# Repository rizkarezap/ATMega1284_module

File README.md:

# ATMega1284 Module
We found that we faced challenges when we got a project that prioritized board size, periperal, and resources. Therefore, we designed a module to facilitate our work. This module uses ATMega1284 as the main control. We also added CP2102 as USB to UART Bridge Virtual COM Port (VCP) drivers. We use a 20MHz oscillator and expand all the ATMega1284 peripherals.

# Board Design
We use KiCAD to design our boards. We include everything for you to be able to develop again.

# Our hope
Actually we really want to print this module. However, we have limited research and resource costs. If you are willing to help us, we will be very grateful. Furthermore, we present everything we have done. Hope you can use it.

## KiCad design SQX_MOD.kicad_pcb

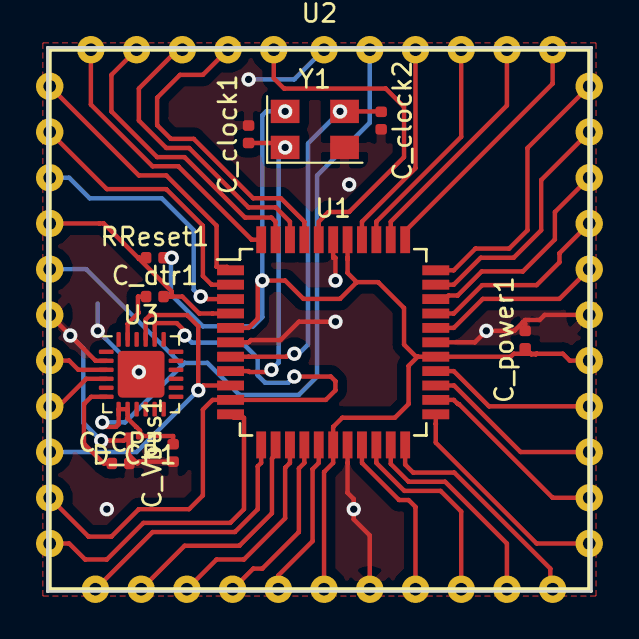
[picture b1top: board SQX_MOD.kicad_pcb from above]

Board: 2 copper layers, 30.2 x 30.2 mm, 12 parts (0 on the bottom side), 42 nets.

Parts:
C_CP1: 100nF; C_0402_1005Metric
C_Vbus1: 4.7pf; C_0402_1005Metric
C_clock1, C_clock2: 22pf; C_0402_1005Metric
C_dtr1: 100Nf; C_0402_1005Metric
C_power1: 100nF; C_0402_1005Metric
D_CP1: D_TVS; D_0201_0603Metric
RReset1: 10K; R_0402_1005Metric
U1: ATmega1284P-AU; TQFP-44_10x10mm_P0.8mm
U2: SQX_MOD; SQX_MOD_SMD
U3: CP2102N-A01-GQFN24; QFN-24-1EP_4x4mm_P0.5mm_EP2.6x2.6mm
Y1: Crystal_GND24; Crystal_SMD_5032-4Pin_5.0x3.2mm

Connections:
AREF: U1.29, U2.AREF
D+: U2.D+, U3.3
D-: U2.D-, U3.4
DTR: C_dtr1.1, U3.23
GND: C_CP1.2, C_Vbus1.1, C_clock1.2, C_clock2.2, C_power1.2, D_CP1.2, U1.6, U1.18, U1.28, U1.39, U2.GND0, U2.GND1, U2.GND2, U2.GND3, U3.2, U3.25, Y1.2
unnamed: C_CP1.1, U3.6
unnamed: C_clock1.1, U1.8, Y1.1
unnamed: C_clock2.1, U1.7, Y1.3
PA0: U1.37, U2.PA0
PA1: U1.36, U2.PA1
PA2: U1.35, U2.PA2
PA3: U1.34, U2.PA3
PA4: U1.33, U2.PA4
PA5: U1.32, U2.PA5
PA6: U1.31, U2.PA6
PA7: U1.30, U2.PA7
PB0: U1.40, U2.PB0
PB1: U1.41, U2.PB1
PB2: U1.42, U2.PB2
PB3: U1.43, U2.PB3
PB4: U1.44, U2.PB4
PB5: U1.1, U2.PB5
PB6: U1.2, U2.PB6
PB7: U1.3, U2.PB7
PC0: U1.19, U2.PC0
PC1: U1.20, U2.PC1
PC2: U1.21, U2.PC2
PC3: U1.22, U2.PC3
PC4: U1.23, U2.PC4
PC5: U1.24, U2.PC5
PC6: U1.25, U2.PC6
PC7: U1.26, U2.PC7
PD2: U1.11, U2.PD2
PD3: U1.12, U2.PD3
PD4: U1.13, U2.PD4
PD5: U1.14, U2.PD5
PD6: U1.15, U2.PD6
PD7: U1.16, U2.PD7
RESET: C_dtr1.2, RReset1.1, U1.4, U2.RESET
RX0: U1.10, U2.PD1, U3.20
TX0: U1.9, U2.PD0, U3.21
VBUS: C_Vbus1.2, C_power1.1, D_CP1.1, RReset1.2, U1.5, U1.17, U1.27, U1.38, U2.VBAT, U2.VBUS, U2.VCC, U3.7, U3.8, Y1.4
